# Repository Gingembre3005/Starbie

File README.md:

# Starbie

## Introduction:

This is my Patrick Star Starbie for the Hackclub Half Life challenge. It's a desktop pet that can interact with the user. I learned a lot doing this project as it was my first time designing a PCB. 

## Firmware:

Patrick Star will have different emotional states, which will change when the user interacts with him. 
If you leave Patrick Star alone for too long he will progressively become sad. 

## How to flash the firmware:

1. Download the code which will soon be in this repo.
2. Download the Arduino IDE.
3. Open File → Preferences. In Additional Boards Manager URLs, add:

https://espressif.github.io/arduino-esp32/package_esp32_index.json

4. Open Tools → Board → Boards Manager, search for esp32, and install esp32 by Espressif Systems.
5. Under Tools → Board → esp32, select XIAO_ESP32C3.
6. Open Sketch → Include Library → Manage Libraries. Install these libraries one at a time:

-Adafruit GFX Library
-Adafruit SSD1306
-Adafruit MPU6050
-DHT sensor library
If Arduino asks to install dependencies, choose Install All.

7. Connect the Patrick Star Starbie to your pc and flash the code.

## PCB picture:

## Schematic picture:

## Picture from a render of the PCB:

## Picture of a drawing for the face of the Starbie:

## Bill of Materials

## Bill of Materials (BOM)

| Qty | Item  | Cost (ea.) (€) | Link |
|---:|---|---:|---|
| 1 | 0.96" OLED |  2.49 | [AliExpress](https://de.aliexpress.com/item/1005007475013244.html?spm=a2g0o.productlist.main.1.6d2014c3TzMwfG&algo_pvid=b96e7c29-bb73-43d6-8ad9-56e24584bb3a&algo_exp_id=b96e7c29-bb73-43d6-8ad9-56e24584bb3a-0&pdp_ext_f=%7B%22order%22%3A%22301%22%2C%22eval%22%3A%221%22%2C%22fromPage%22%3A%22search%22%7D&pdp_npi=6%40dis%21EUR%212.51%212.49%21%21%2118.18%2118.03%21%40210398e917931961607873221e0ccd%2112000040902623417%21sea%21DE%218427292374%21ABX%211%210%21n_tag%3A-29910%3Bd%3Aaf2815fb%3Bm03_new_user%3A-29895&curPageLogUid=0JzHXNCRZCjm&utparam-url=scene%3Asearch%7Cquery_from%3A%7Cx_object_id%3A1005007475013244%7C_p_origin_prod%3A) |
| 1 | MPU6050 | 2.15 | [AliExpress](https://de.aliexpress.com/item/1005009925487659.html?spm=a2g0o.productlist.main.2.75f215f9KceZsF&algo_pvid=6fdad029-dce3-4cbe-8554-f53b04c18259&algo_exp_id=6fdad029-dce3-4cbe-8554-f53b04c18259-1&pdp_ext_f=%7B%22order%22%3A%2296%22%2C%22eval%22%3A%221%22%2C%22fromPage%22%3A%22search%22%7D&pdp_npi=6%40dis%21EUR%212.15%212.15%21%21%2115.57%2115.57%21%400b88ad2b17931962859502002e0d3c%2112000050595570254%21sea%21DE%218427292374%21ABX%211%210%21n_tag%3A-29910%3Bd%3Aaf2815fb%3Bm03_new_user%3A-29895&curPageLogUid=cu7F5WUZFwko&utparam-url=scene%3Asearch%7Cquery_from%3A%7Cx_object_id%3A1005009925487659%7C_p_origin_prod%3A) |
| 1 | 220 Ω Resistor |  0.18 | [AliExpress](https://de.aliexpress.com/item/1005011886443911.html?spm=a2g0o.productlist.seoads.1.1e2c4710u1212S&p4p_pvid=202610280705232452802854227200000752280_1&gatewayAdapt=glo2deu) |
| 1 | 10 kΩ Resistor |  0.12 | [AliExpress](https://de.aliexpress.com/item/1005011886443911.html?spm=a2g0o.productlist.seoads.1.1e2c4710u1212S&p4p_pvid=202610280705232452802854227200000752280_1&gatewayAdapt=glo2deu) |
| 2 | MX Switches |  0.59 | [AliExpress](https://de.aliexpress.com/item/1005008089864080.html?spm=a2g0o.productlist.main.5.5f5726b3voFLSQ&algo_pvid=8267b3ce-ddf8-4c52-89a3-403fe741ac14&algo_exp_id=8267b3ce-ddf8-4c52-89a3-403fe741ac14-4&pdp_ext_f=%7B%22order%22%3A%22234%22%2C%22eval%22%3A%221%22%2C%22fromPage%22%3A%22search%22%7D&pdp_npi=6%40dis%21EUR%212.99%212.99%21%21%2121.65%2121.65%21%40210382de17931964906297733e0e7a%2112000045838677521%21sea%21DE%218427292374%21ABX%211%210%21n_tag%3A-29910%3Bd%3Aaf2815fb%3Bm03_new_user%3A-29895&curPageLogUid=SBpjzuD7hhLL&utparam-url=scene%3Asearch%7Cquery_from%3A%7Cx_object_id%3A1005008089864080%7C_p_origin_prod%3A) |
| 1 | EC11E Rotary Encoder | 1.59 | [AliExpress](https://de.aliexpress.com/item/1005007943273440.html?spm=a2g0o.productlist.main.2.3e352854TYahRC&algo_pvid=362d8240-3916-4fa6-bdb1-5f0cd205c7fd&algo_exp_id=362d8240-3916-4fa6-bdb1-5f0cd205c7fd-1&pdp_ext_f=%7B%22order%22%3A%2288%22%2C%22eval%22%3A%221%22%2C%22fromPage%22%3A%22search%22%7D&pdp_npi=6%40dis%21EUR%211.61%211.59%21%21%2111.64%2111.52%21%400b15834017931965231023985e0c30%2112000042956357427%21sea%21DE%218427292374%21ABX%211%210%21n_tag%3A-29910%3Bd%3Aaf2815fb%3Bm03_new_user%3A-29895&curPageLogUid=u6MvxcbNVg3o&utparam-url=scene%3Asearch%7Cquery_from%3A%7Cx_object_id%3A1005007943273440%7C_p_origin_prod%3A) |
| 1 | XIAO ESP32-C3 | 6.79 | [AliExpress](https://de.aliexpress.com/item/1005008791664713.html?spm=a2g0o.productlist.main.3.30005505pPruuk&algo_pvid=92206ada-f1b0-413d-841b-35a86a931050&algo_exp_id=92206ada-f1b0-413d-841b-35a86a931050-2&pdp_ext_f=%7B%22order%22%3A%22448%22%2C%22spu_best_type%22%3A%22price%22%2C%22eval%22%3A%221%22%2C%22fromPage%22%3A%22search%22%7D&pdp_npi=6%40dis%21EUR%216.82%216.79%21%21%217.41%217.37%21%400b15831117931966898396804e0e5e%2112000046678458240%21sea%21DE%218427292374%21ABX%211%210%21n_tag%3A-29910%3Bd%3Aaf2815fb%3Bm03_new_user%3A-29895&curPageLogUid=czxJjWamX9rY&utparam-url=scene%3Asearch%7Cquery_from%3A%7Cx_object_id%3A1005008791664713%7C_p_origin_prod%3A) |
| 1 | DHT11 | 0.81 | [AliExpress](https://de.aliexpress.com/item/1005012263106656.html?spm=a2g0o.productlist.main.4.317233bb8PGG5t&aem_p4p_detail=2026102807094916533218519186180000795316&algo_pvid=b15d7c45-9a97-4939-a3b2-d946b97b6013&algo_exp_id=b15d7c45-9a97-4939-a3b2-d946b97b6013-3&pdp_ext_f=%7B%22order%22%3A%2273%22%2C%22eval%22%3A%221%22%2C%22fromPage%22%3A%22search%22%7D&pdp_npi=6%40dis%21EUR%210.81%210.81%21%21%215.88%215.88%21%400b15831117931965899034786e0db9%2112000057911460838%21sea%21DE%218427292374%21ABX%211%210%21n_tag%3A-29910%3Bd%3Aaf2815fb%3Bm03_new_user%3A-29895&curPageLogUid=yzPnKeN2s9ud&utparam-url=scene%3Asearch%7Cquery_from%3A%7Cx_object_id%3A1005012263106656%7C_p_origin_prod%3A&search_p4p_id=2026102807094916533218519186180000795316_1) |
| 1 | Buzzer  | 0.18 | [AliExpress](https://de.aliexpress.com/item/1005007274812383.html?spm=a2g0o.productlist.main.3.29336836oNOM0O&algo_pvid=c6c6338f-83eb-40f7-8122-7b515315e1f6&algo_exp_id=c6c6338f-83eb-40f7-8122-7b515315e1f6-2&pdp_ext_f=%7B%22order%22%3A%221484%22%2C%22spu_best_type%22%3A%22price%22%2C%22eval%22%3A%221%22%2C%22fromPage%22%3A%22search%22%7D&pdp_npi=6%40dis%21EUR%215.44%211.79%21%21%2139.39%2112.98%21%400b884a9917931966218307045e0dd7%2112000040029049663%21sea%21DE%218427292374%21ABX%211%210%21n_tag%3A-29910%3Bd%3Aaf2815fb%3Bm03_new_user%3A-29895&curPageLogUid=CHnwAKqXDZEr&utparam-url=scene%3Asearch%7Cquery_from%3A%7Cx_object_id%3A1005007274812383%7C_p_origin_prod%3A) |
| 1 | PCB  | 10.00 | [JLCPCB](https://www.jlcpcb.com/) |
| | **Total (per kit)** | | **24.9** | |

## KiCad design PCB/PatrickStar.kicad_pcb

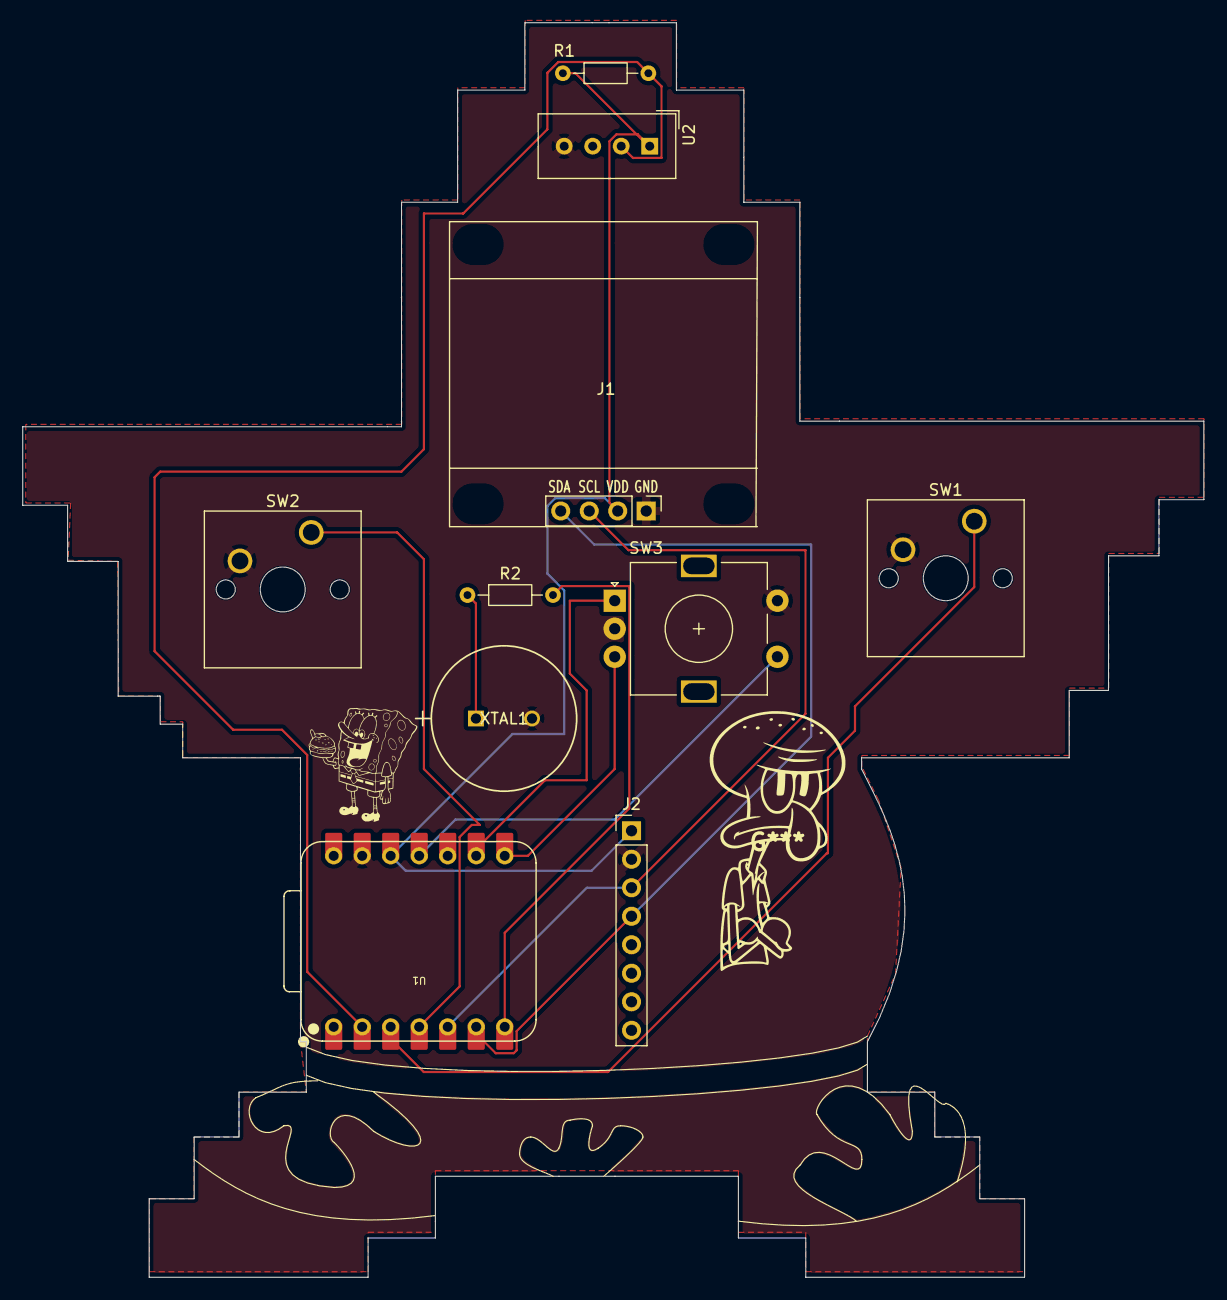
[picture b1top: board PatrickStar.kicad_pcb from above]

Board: 2 copper layers, 105.2 x 111.8 mm, 10 parts (0 on the bottom side), 11 nets.

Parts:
J1: Conn_01x04_Pin; Display_128x64_096_I2C
J2: Conn_01x08_Pin; PinHeader_1x08_P2.54mm_Vertical
R1: 10k; R_Axial_DIN0204_L3.6mm_D1.6mm_P7.62mm_Horizontal
R2: 220; R_Axial_DIN0204_L3.6mm_D1.6mm_P7.62mm_Horizontal
SW1, SW2: SW_Push; SW_Cherry_MX_1.00u_PCB
SW3: RotaryEncoder_Switch; RotaryEncoder_Alps_EC11E-Switch_Vertical_H20mm
U1: XIAO-ESP32-C3-SMD; XIAO-ESP32-C6-DIP
U2: DHT11; Aosong_DHT11_5.5x12.0_P2.54mm
XTAL1: PS1240P02BT; XTAL_PS1240P02BT_TDK

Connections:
+3.3V: J1.2, J2.1, R1.1, R2.1, U1.12 (3V3_OUT), U2.1 (VDD), XTAL1.1
/DHT11 DATA: R1.2, U1.2 (D1), U2.2 (DATA)
/GPIO2: SW1.1, U1.3 (D2)
/GPIO3: SW2.1, U1.4 (D3)
/GPIO 6: R2.2, U1.7 (D6)
/SCL: J1.3, J2.3, U1.5 (D4)
/SDA: J1.4, J2.4, U1.6 (D5)
EC11A: SW3.A, U1.9 (D8)
EC11B: SW3.B, U1.8 (D7)
EC11SWB: SW3.S1, U1.11 (D10)
GND: J1.1, J2.2, SW1.2, SW2.2, SW3.C, SW3.S2, U1.13 (GND), U2.4 (GND), XTAL1.2
